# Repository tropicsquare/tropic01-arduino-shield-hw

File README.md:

# TROPIC01 Arduino Shield

This repository contains the design files for the TROPIC01 development shield, designed for the Arduino form factor. Each folder corresponds to a specific PCB revision.

### About TROPIC01

For more information about the TROPIC01 secure element, please see the official documentation:

*   [TROPIC01 Datasheet](https://github.com/tropicsquare/tropic01/tree/main/doc/datasheet)
*   [TROPIC01 Website](https://www.tropicsquare.com/tropic01)

# Arduino Shield's Versions

Following table shows all versions of distributed shields.

| hw revision    | Picture                                                                                                            |
|----------------|----------------------------------------|
| 1401           |  [Top](./TS1401_design/img/top.png)    |

# Getting Started

To interact with the TROPIC01 chip on STM32-based systems we provide the [`libtropic-stm32`](https://github.com/tropicsquare/libtropic-stm32) repository, containing integration examples of our platform-independent SDK, [`libtropic`](https://github.com/tropicsquare/libtropic).

 > [!IMPORTANT]
 > Before you start with various examples, we strongly recommend to do two things first:
 > * Read CHIP ID and TROPIC01's firmware versions and **save printed output for future reference**
 > * Update TROPIC01's both internal firmware to latest version.

In [`libtropic-stm32`](https://github.com/tropicsquare/libtropic-stm32) repository, you can find specifice instruction for both operations based on hardware you use.

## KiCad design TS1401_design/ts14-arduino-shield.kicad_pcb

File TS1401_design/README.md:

# About

TS14 – TROPIC01 Arduino Shield
A KiCad-based hardware project designed to interface the TROPIC01 device with standard Arduino development boards.

This shield allows easy integration of TROPIC01 into Arduino-based environments for development, testing, and prototyping.
It is intended for internal use and partner evaluation setups, following the Arduino mechanical and electrical interface.

# Project structure

* `*.kicad_pro` - KiCad project file
* `*.kicad_sch` - Schematic file
* `*.kicad_pcb` - PCB layout file
* `./out/` -  Generated Gerber files for PCB manufacturing
* `./bom/` - Bill of materials, including order codes and interactive BOM
* `./img/` - Images (e.g. PCB renders)
* `*_schematics.pdf` - Exported schematic diagrams (latest version)

# Manufacturing instructions:

## Assembly

IC1/CON1: Chose one variant, assembly IC1 or CON1 (not both on one board).
Chose `bom/bom_variant_*`.

Because Arduino boards use female sockets, the shield's connectors must be mounted on the top side 
to allow the pins to extend through to the bottom side for proper connection. \

There are no any special requirements for C and R components.
Where not specified the R tolerance is 5% and C 20%.

## PCB

* Number of cu layers: 2
* Board Thickness: 1.6
* Core: FR4
* Size: 58 x 53mm
* Mask: Blue
* Silkscreen: Yes (TOP only)

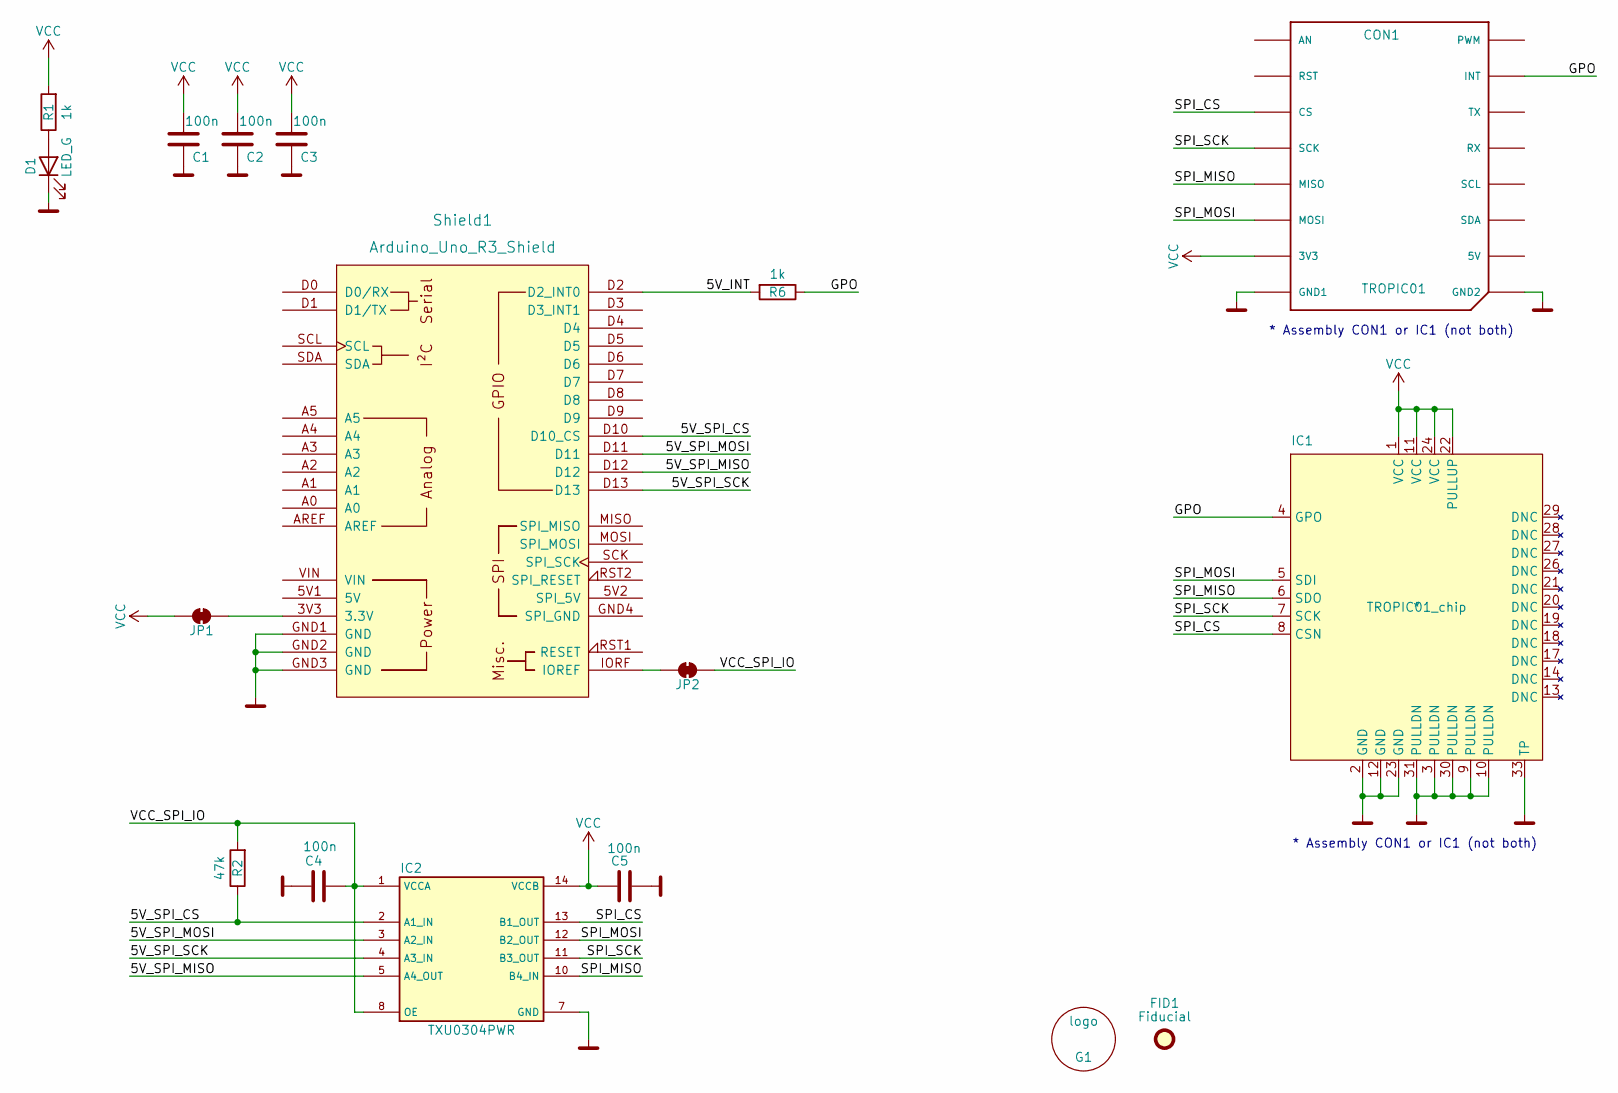
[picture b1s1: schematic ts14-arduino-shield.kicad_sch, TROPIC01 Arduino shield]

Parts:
C1, C2, C3, C4, C5: 100n; C_0805_2012Metric_Pad1.18x1.45mm_HandSolder
CON1: TROPIC01; TROPIC01_mikrobus
D1: LED_G; LED_0805_2012Metric
FID1: Fiducial; Fiducial_0.5mm_Mask1mm
G1: logo; tropicsquare_logo
IC1: TROPIC01_chip; QFN-32-1EP_4x4mm_P0.4mm_EP2.65x2.65mm
IC2: TXU0304PWR; TSSOP-14_4.4x5mm_P0.65mm
JP1, JP2: SolderJumper_2_Bridged; SolderJumper-2_P1.3mm_Bridged
R1, R6: 1k; R_0805_2012Metric_Pad1.20x1.40mm_HandSolder
R2: 47k; R_0805_2012Metric_Pad1.20x1.40mm_HandSolder
Shield1: Arduino_Uno_R3_Shield

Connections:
/5V_INT: R6.2, Shield1.D2 (D2_INT0)
/5V_SPI_CS: IC2.2 (A1_IN), R2.1, Shield1.D10 (D10_CS)
/5V_SPI_MISO: IC2.5 (A4_OUT), Shield1.D12
/5V_SPI_MOSI: IC2.3 (A2_IN), Shield1.D11
/5V_SPI_SCK: IC2.4 (A3_IN), Shield1.D13
/GPO: CON1.P15 (INT), IC1.4 (GPO), R6.1
/SPI_CS: CON1.P3 (CS), IC1.8 (CSN), IC2.13 (B1_OUT)
/SPI_MISO: CON1.P5 (MISO), IC1.6 (SDO), IC2.10 (B4_IN)
/SPI_MOSI: CON1.P6 (MOSI), IC1.5 (SDI), IC2.12 (B2_OUT)
/SPI_SCK: CON1.P4 (SCK), IC1.7 (SCK), IC2.11 (B3_OUT)
/VCC_SPI_IO: C4.1, IC2.1 (VCCA), IC2.8 (OE), JP2.1 (A), R2.2
GND: C1.1, C2.1, C3.1, C4.2, C5.1, CON1.P8 (GND1), CON1.P9 (GND2), D1.1 (K), IC1.2 (GND), IC1.3 (PULLDN), IC1.9 (PULLDN), IC1.10 (PULLDN), IC1.12 (GND), IC1.23 (GND), IC1.30 (PULLDN), IC1.31 (PULLDN), IC1.33 (TP), IC2.7 (GND), Shield1.GND1 (GND), Shield1.GND2 (GND), Shield1.GND3 (GND)
unnamed: D1.2 (A), R1.1
unnamed: JP1.1 (A), Shield1.3V3 (3.3V)
unnamed: JP2.2 (B), Shield1.IORF (IOREF)
VCC: C1.2, C2.2, C3.2, C5.2, CON1.P7 (3V3), IC1.1 (VCC), IC1.11 (VCC), IC1.22 (PULLUP), IC1.24 (VCC), IC2.14 (VCCB), JP1.2 (B), R1.2

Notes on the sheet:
* Assembly CON1 or IC1 (not both)

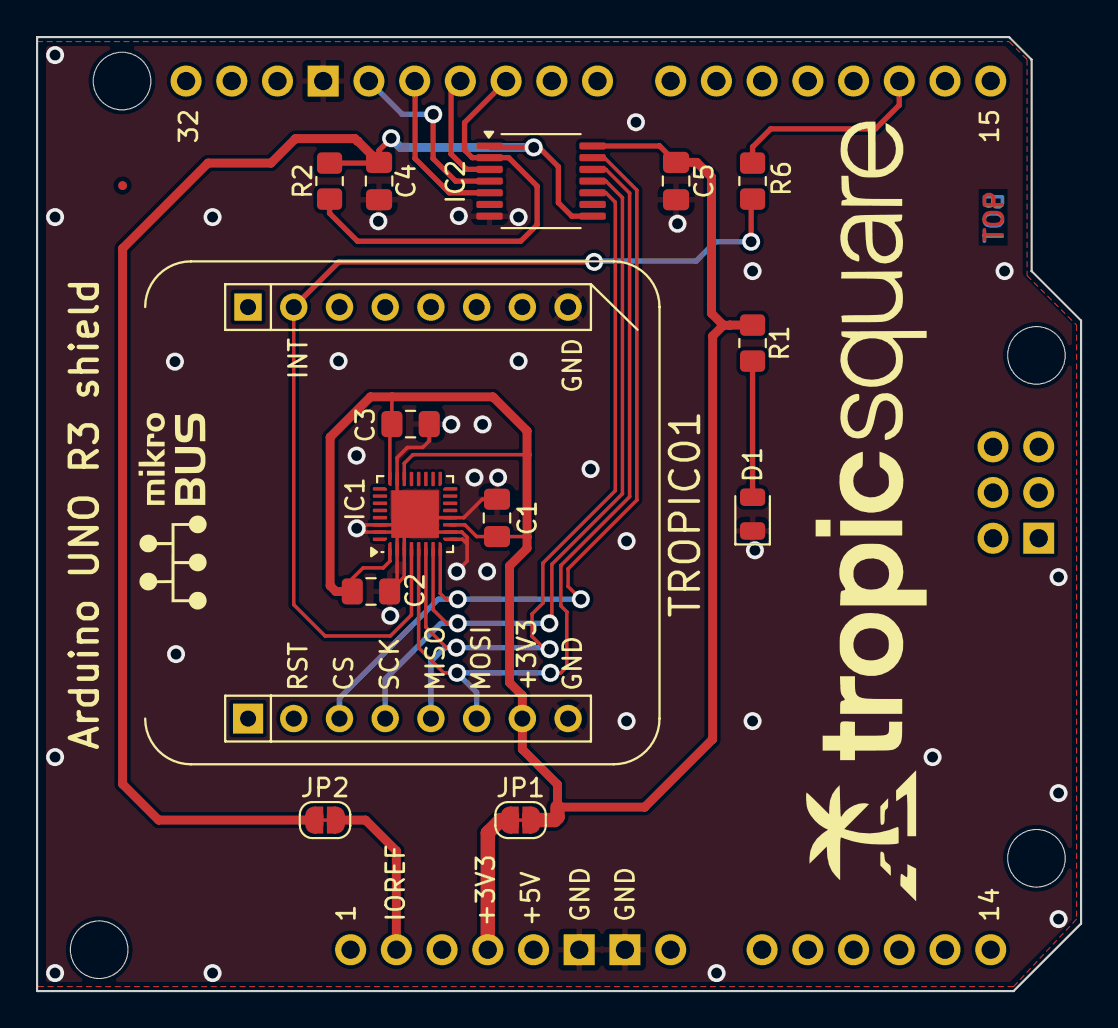
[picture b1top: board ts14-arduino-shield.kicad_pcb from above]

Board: 2 copper layers, 58.0 x 53.0 mm, 17 parts (0 on the bottom side), 16 nets.

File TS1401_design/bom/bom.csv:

"Reference","Value","Footprint","Qty","DNP","OC_MOUSER"
"C1,C2,C3,C4,C5","100n","Capacitor_SMD:C_0805_2012Metric_Pad1.18x1.45mm_HandSolder","5","","187-CL21B104KBFNNNE"
"CON1","TROPIC01","ts_mikrobus:TROPIC01_mikrobus","1","","* 932-MIKROE-4247"
"D1","LED_G","LED_SMD:LED_0805_2012Metric","1","","710-150080GS75000"
"IC1","TROPIC01_chip","tropic01_chip:QFN-32-1EP_4x4mm_P0.4mm_EP2.65x2.65mm","1","","* "
"IC2","TXU0304PWR","Package_SO:TSSOP-14_4.4x5mm_P0.65mm","1","","595-TXU0304PWR"
"R1,R6","1k","Resistor_SMD:R_0805_2012Metric_Pad1.20x1.40mm_HandSolder","2","","603-RC0805JR-071KL"
"R2","47k","Resistor_SMD:R_0805_2012Metric_Pad1.20x1.40mm_HandSolder","1","","603-RC0805JR-0747KL"
"Shield1","Arduino_Uno_R3_Shield","shields:Arduino_Uno_R3_Shield","1",""," 474-PRT-11417 (set of 4 connectors)"

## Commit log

2025-12-10 Fix: Update BOM to fix wrong assembly of MIKROE socket
2025-12-10 fix: remove obsolete BOM file
